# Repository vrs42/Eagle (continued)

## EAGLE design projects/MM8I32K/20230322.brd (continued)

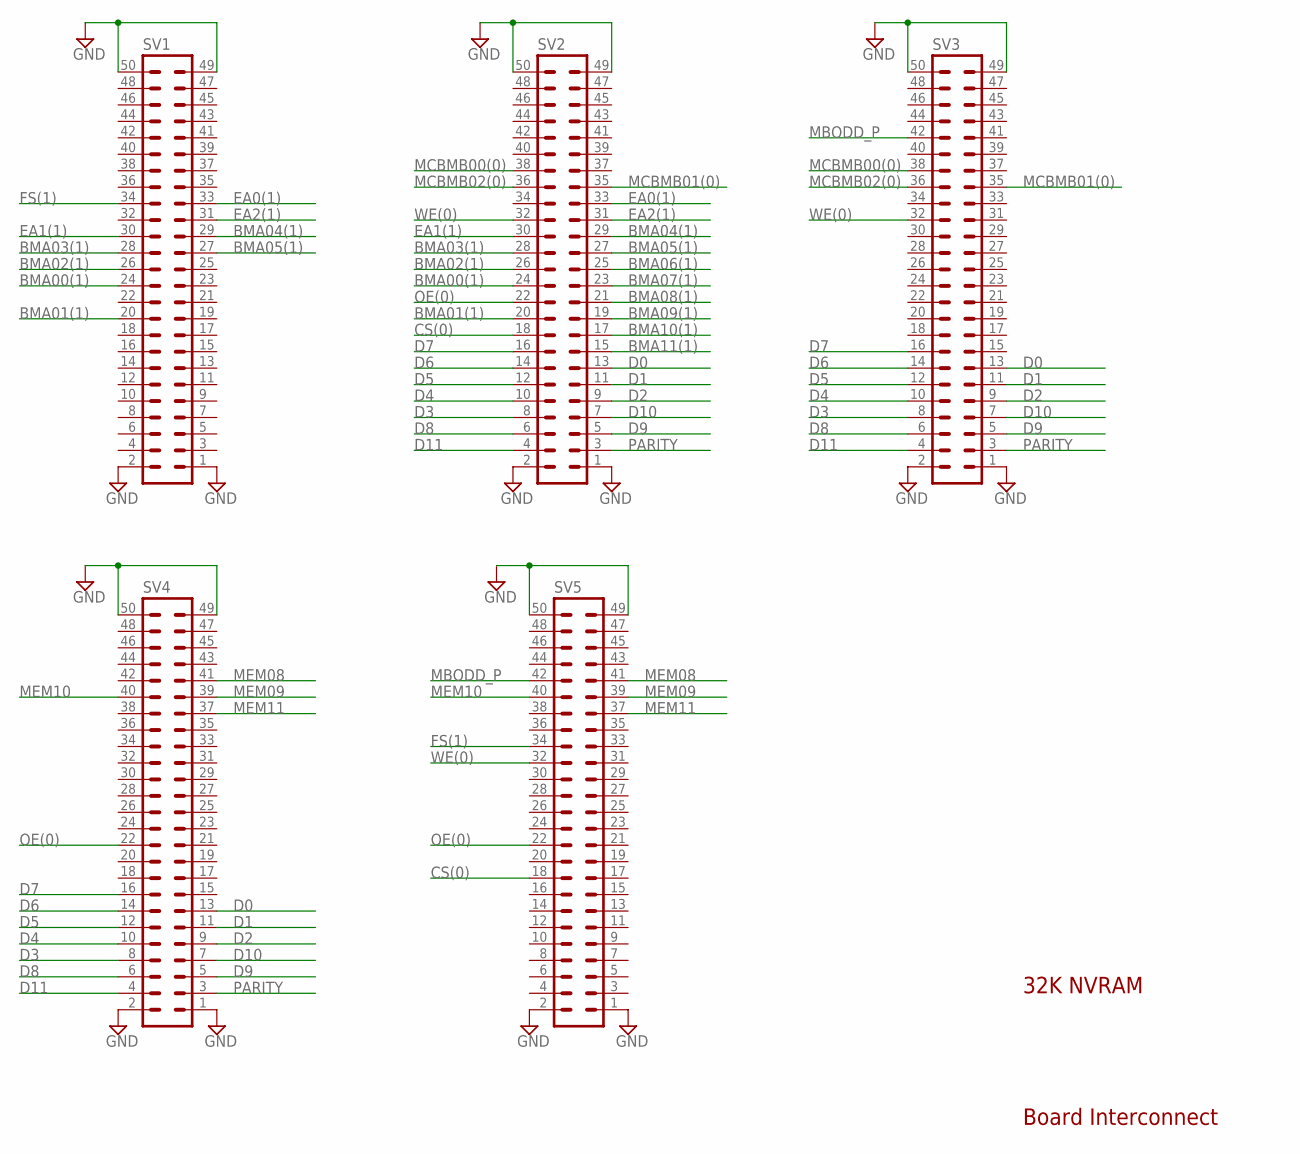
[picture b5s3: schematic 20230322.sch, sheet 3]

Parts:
SV1, SV2, SV3, SV4, SV5: ML50L

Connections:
BMA00(1): SV1.24, SV2.24; also elsewhere on the board
BMA01(1): SV1.20, SV2.20; also elsewhere on the board
BMA02(1): SV1.26, SV2.26; also elsewhere on the board
BMA03(1): SV1.28, SV2.28; also elsewhere on the board
BMA04(1): SV1.29, SV2.29; also elsewhere on the board
BMA05(1): SV1.27, SV2.27; also elsewhere on the board
BMA06(1): SV2.25; also elsewhere on the board
BMA07(1): SV2.23; also elsewhere on the board
BMA08(1): SV2.21; also elsewhere on the board
BMA09(1): SV2.19; also elsewhere on the board
BMA10(1): SV2.17; also elsewhere on the board
BMA11(1): SV2.15; also elsewhere on the board
CS(0): SV2.18, SV5.18; also elsewhere on the board
D0: SV2.13, SV3.13, SV4.13; also elsewhere on the board
D1: SV2.11, SV3.11, SV4.11; also elsewhere on the board
D2: SV2.9, SV3.9, SV4.9; also elsewhere on the board
D3: SV2.8, SV3.8, SV4.8; also elsewhere on the board
D4: SV2.10, SV3.10, SV4.10; also elsewhere on the board
D5: SV2.12, SV3.12, SV4.12; also elsewhere on the board
D6: SV2.14, SV3.14, SV4.14; also elsewhere on the board
D7: SV2.16, SV3.16, SV4.16; also elsewhere on the board
D8: SV2.6, SV3.6, SV4.6; also elsewhere on the board
D9: SV2.5, SV3.5, SV4.5; also elsewhere on the board
D10: SV2.7, SV3.7, SV4.7; also elsewhere on the board
D11: SV2.4, SV3.4, SV4.4; also elsewhere on the board
EA0(1): SV1.33, SV2.33; also elsewhere on the board
EA1(1): SV1.30, SV2.30; also elsewhere on the board
EA2(1): SV1.31, SV2.31; also elsewhere on the board
FS(1): SV1.34, SV5.34; also elsewhere on the board
GND: SV1.1, SV1.2, SV1.49, SV1.50, SV2.1, SV2.2, SV2.49, SV2.50, SV3.1, SV3.2, SV3.49, SV3.50, SV4.1, SV4.2, SV4.49, SV4.50, SV5.1, SV5.2, SV5.49, SV5.50; also elsewhere on the board
MBODD_P: SV3.42, SV5.42; also elsewhere on the board
MCBMB00(0): SV2.38, SV3.38; also elsewhere on the board
MCBMB01(0): SV2.35, SV3.35; also elsewhere on the board
MCBMB02(0): SV2.36, SV3.36; also elsewhere on the board
MEM08: SV4.41, SV5.41; also elsewhere on the board
MEM09: SV4.39, SV5.39; also elsewhere on the board
MEM10: SV4.40, SV5.40; also elsewhere on the board
MEM11: SV4.37, SV5.37; also elsewhere on the board
OE(0): SV2.22, SV4.22, SV5.22; also elsewhere on the board
PARITY: SV2.3, SV3.3, SV4.3; also elsewhere on the board
WE(0): SV2.32, SV3.32, SV5.32; also elsewhere on the board

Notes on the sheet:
32K NVRAM
Board Interconnect

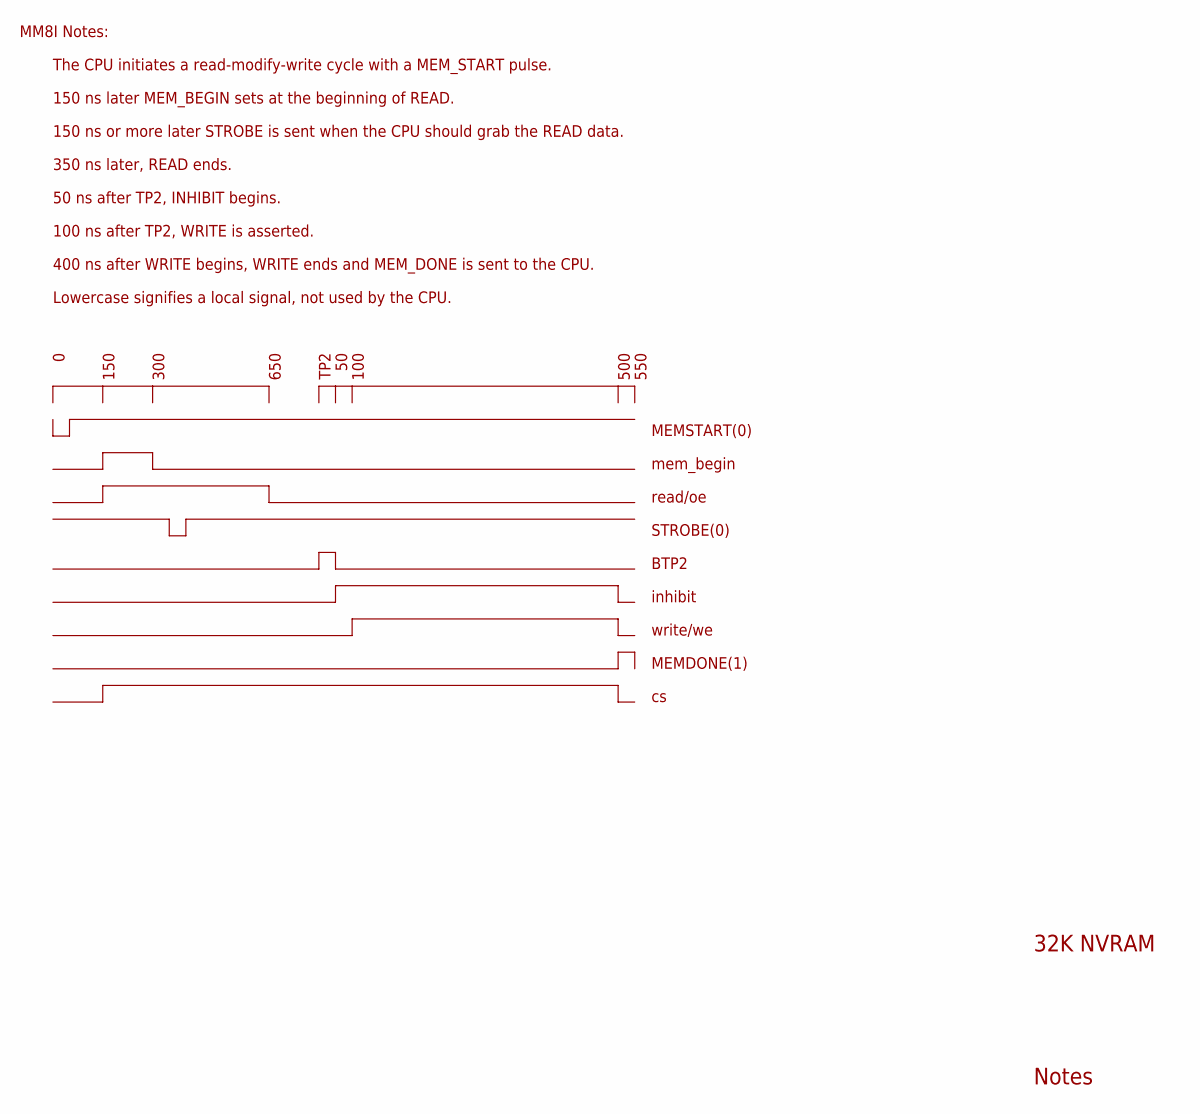
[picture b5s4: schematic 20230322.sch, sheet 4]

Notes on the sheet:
32K NVRAM
Notes
The CPU initiates a read-modify-write cycle with a MEM_START pulse.
150 ns later MEM_BEGIN sets at the beginning of READ.
150 ns or more later STROBE is sent when the CPU should grab the READ data.
50 ns after TP2, INHIBIT begins.
100 ns after TP2, WRITE is asserted.
400 ns after WRITE begins, WRITE ends and MEM_DONE is sent to the CPU.
350 ns later, READ ends.
150
300
650
TP2
100
500
MEMSTART(0)
mem_begin
read/oe
STROBE(0)
BTP2
inhibit
write/we
MEMDONE(1)
Lowercase signifies a local signal, not used by the CPU.
550
MM8I Notes:

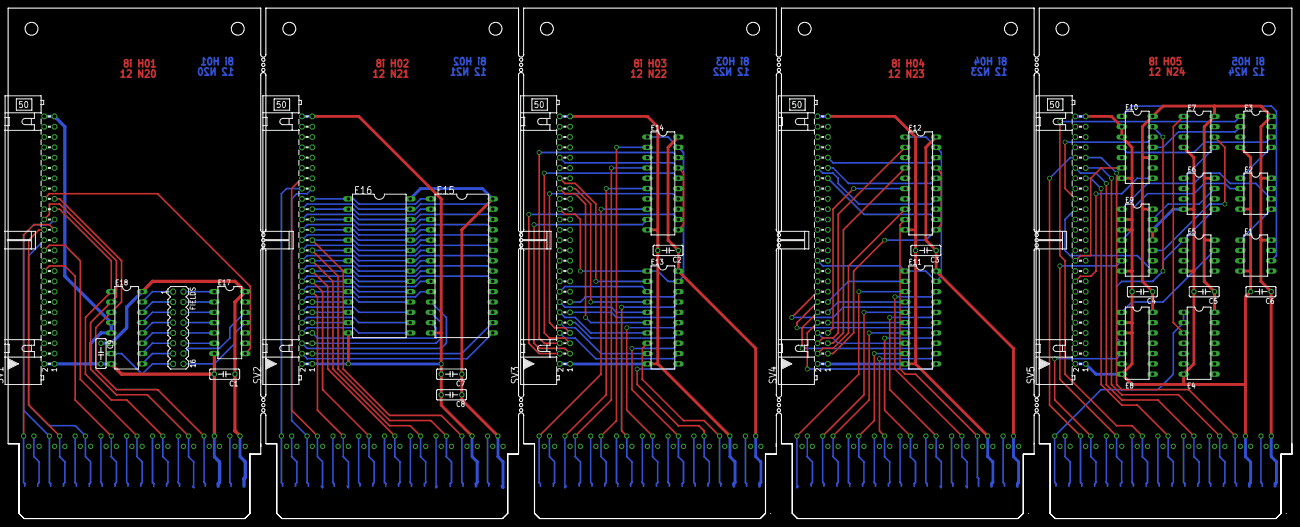
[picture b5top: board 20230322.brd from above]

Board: 2 copper layers, 316.2 x 125.7 mm, 44 parts (0 on the bottom side), 128 nets.

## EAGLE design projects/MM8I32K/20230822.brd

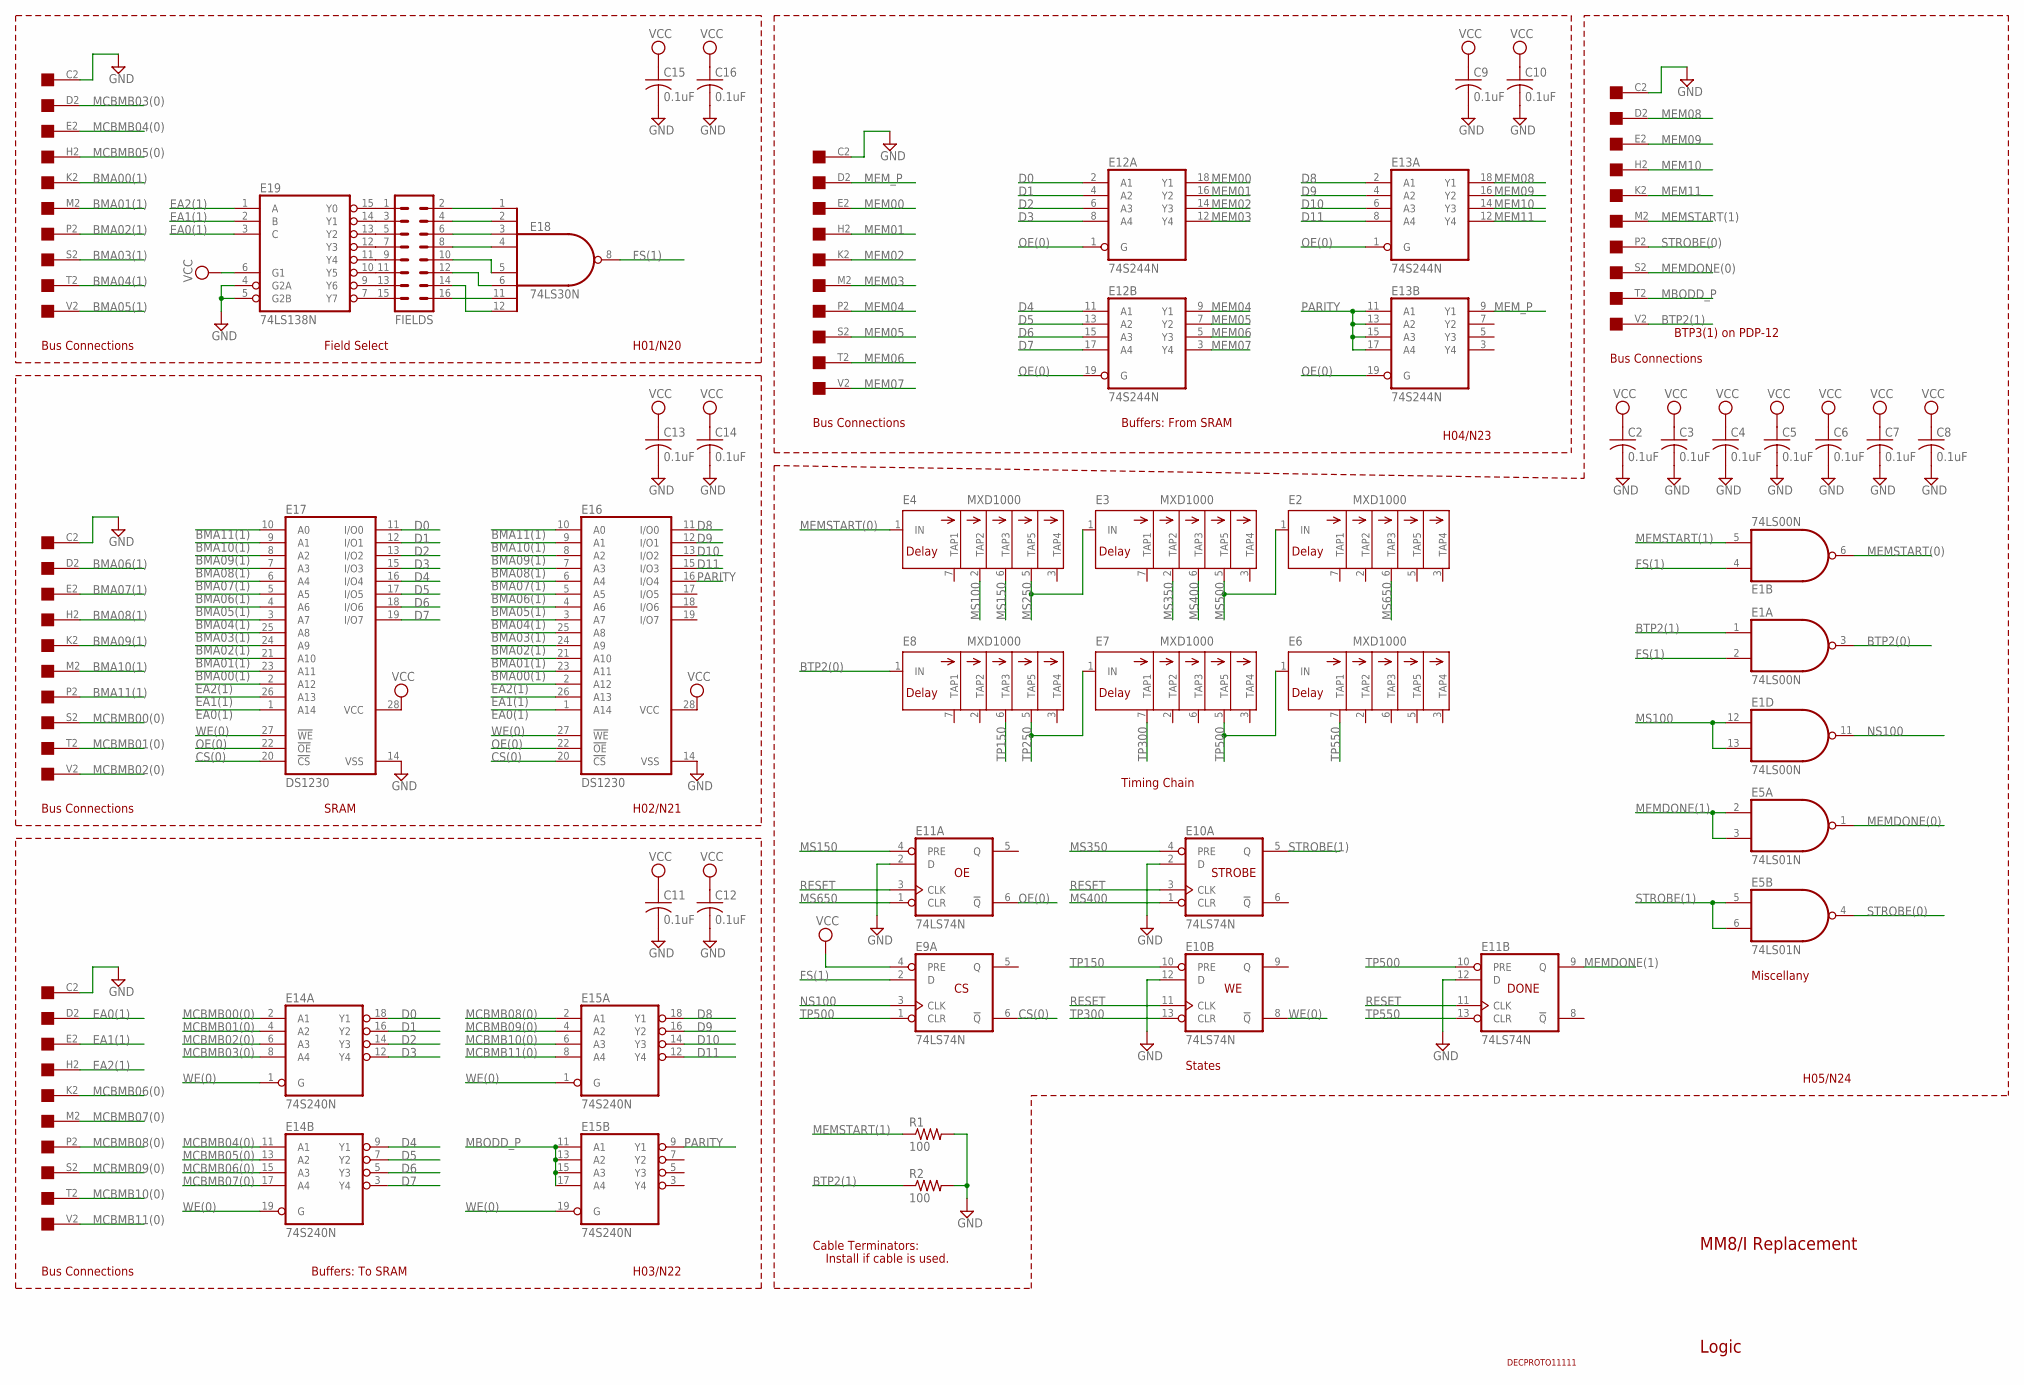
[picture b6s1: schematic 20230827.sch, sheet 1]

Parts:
C2, C3, C4, C5, C6, C7, C8, C9, C10, C11, C12, C13, C14, C15, C16: 0.1uF; C050-025X075
E1: 74LS00N; DIL14
E2, E3, E4, E6, E7, E8: MXD1000; DIL08
E5: 74LS01N; DIL14
E9, E10, E11: 74LS74N; DIL14
E12, E13: 74S244N; DIL20
E14, E15: 74S240N; DIL20
E16, E17: DS1230; DIL28-6
E18: 74LS30N; DIL14
E19: 74LS138N; DIL16
FIELDS: MA08-2
H01, H02, H03, H04, H05: EDGE-CON1
R1, R2: 100; 0207/10
U$6: DECPROTO11111

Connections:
BMA00(1): E16.23 (A11), E17.23 (A11), H01.K2; also elsewhere on the board
BMA01(1): E16.21 (A10), E17.21 (A10), H01.M2; also elsewhere on the board
BMA02(1): E16.24 (A9), E17.24 (A9), H01.P2; also elsewhere on the board
BMA03(1): E16.25 (A8), E17.25 (A8), H01.S2; also elsewhere on the board
BMA04(1): E16.3 (A7), E17.3 (A7), H01.T2; also elsewhere on the board
BMA05(1): E16.4 (A6), E17.4 (A6), H01.V2; also elsewhere on the board
BMA06(1): E16.5 (A5), E17.5 (A5), H02.D2; also elsewhere on the board
BMA07(1): E16.6 (A4), E17.6 (A4), H02.E2; also elsewhere on the board
BMA08(1): E16.7 (A3), E17.7 (A3), H02.H2; also elsewhere on the board
BMA09(1): E16.8 (A2), E17.8 (A2), H02.K2; also elsewhere on the board
BMA10(1): E16.9 (A1), E17.9 (A1), H02.M2; also elsewhere on the board
BMA11(1): E16.10 (A0), E17.10 (A0), H02.P2; also elsewhere on the board
BTP2(0): E1.3 (O), E8.1 (IN); also elsewhere on the board
BTP2(1): E1.1 (I0), H05.V2, R2.1
CS(0): E9.6 (!Q), E16.20 (!CS), E17.20 (!CS); also elsewhere on the board
D0: E12.2 (A1), E14.18 (Y1), E17.11 (I/O0); also elsewhere on the board
D1: E12.4 (A2), E14.16 (Y2), E17.12 (I/O1); also elsewhere on the board
D2: E12.6 (A3), E14.14 (Y3), E17.13 (I/O2); also elsewhere on the board
D3: E12.8 (A4), E14.12 (Y4), E17.15 (I/O3); also elsewhere on the board
D4: E12.11 (A1), E14.9 (Y1), E17.16 (I/O4); also elsewhere on the board
D5: E12.13 (A2), E14.7 (Y2), E17.17 (I/O5); also elsewhere on the board
D6: E12.15 (A3), E14.5 (Y3), E17.18 (I/O6); also elsewhere on the board
D7: E12.17 (A4), E14.3 (Y4), E17.19 (I/O7); also elsewhere on the board
D8: E13.2 (A1), E15.18 (Y1), E16.11 (I/O0); also elsewhere on the board
D9: E13.4 (A2), E15.16 (Y2), E16.12 (I/O1); also elsewhere on the board
D10: E13.6 (A3), E15.14 (Y3), E16.13 (I/O2); also elsewhere on the board
D11: E13.8 (A4), E15.12 (Y4), E16.15 (I/O3); also elsewhere on the board
EA0(1): E16.1 (A14), E17.1 (A14), E19.3 (C), H03.D2; also elsewhere on the board
EA1(1): E16.26 (A13), E17.26 (A13), E19.2 (B), H03.E2; also elsewhere on the board
EA2(1): E16.2 (A12), E17.2 (A12), E19.1 (A), H03.H2; also elsewhere on the board
MBODD_P: E15.11 (A1), E15.13 (A2), E15.15 (A3), E15.17 (A4), H05.T2; also elsewhere on the board
MCBMB00(0): E14.2 (A1), H02.S2; also elsewhere on the board
MCBMB01(0): E14.4 (A2), H02.T2; also elsewhere on the board
MCBMB02(0): E14.6 (A3), H02.V2; also elsewhere on the board
MCBMB03(0): E14.8 (A4), H01.D2; also elsewhere on the board
MCBMB04(0): E14.11 (A1), H01.E2; also elsewhere on the board
MCBMB05(0): E14.13 (A2), H01.H2; also elsewhere on the board
MCBMB06(0): E14.15 (A3), H03.K2
MCBMB07(0): E14.17 (A4), H03.M2
MCBMB08(0): E15.2 (A1), H03.P2
MCBMB09(0): E15.4 (A2), H03.S2
MCBMB10(0): E15.6 (A3), H03.T2
MCBMB11(0): E15.8 (A4), H03.V2
MEM00: E12.18 (Y1), H04.E2
MEM01: E12.16 (Y2), H04.H2
MEM02: E12.14 (Y3), H04.K2
MEM03: E12.12 (Y4), H04.M2
MEM04: E12.9 (Y1), H04.P2
MEM05: E12.7 (Y2), H04.S2
MEM06: E12.5 (Y3), H04.T2
MEM07: E12.3 (Y4), H04.V2
MEM08: E13.18 (Y1), H05.D2; also elsewhere on the board
MEM09: E13.16 (Y2), H05.E2; also elsewhere on the board
MEM10: E13.14 (Y3), H05.H2; also elsewhere on the board
MEM11: E13.12 (Y4), H05.K2; also elsewhere on the board
MEMDONE(0): E5.1 (O), H05.S2
MEMDONE(1): E5.2 (I0), E5.3 (I1), E11.9 (Q); also elsewhere on the board
MEMSTART(0): E1.6 (O), E4.1 (IN); also elsewhere on the board
MEMSTART(1): E1.5 (I1), H05.M2, R1.1
MEM_P: E13.9 (Y1), H04.D2
MS100: E1.12 (I0), E1.13 (I1), E4.2 (TAP2)
MS150: E4.6 (TAP3), E11.4 (PRE)
MS250: E3.1 (IN), E4.5 (TAP5)
MS350: E3.2 (TAP2), E10.4 (PRE)
MS400: E3.6 (TAP3), E10.1 (CLR)
MS500: E2.1 (IN), E3.5 (TAP5)
MS650: E2.6 (TAP3), E11.1 (CLR)
unnamed: E19.15 (Y0), FIELDS.1
unnamed: E19.14 (Y1), FIELDS.3
unnamed: E19.13 (Y2), FIELDS.5
unnamed: E19.12 (Y3), FIELDS.7
unnamed: E19.11 (Y4), FIELDS.9
unnamed: E19.10 (Y5), FIELDS.11
unnamed: E19.9 (Y6), FIELDS.13
unnamed: E19.7 (Y7), FIELDS.15
unnamed: E18.4 (I3), FIELDS.8
unnamed: E18.3 (I2), FIELDS.6
unnamed: E18.2 (I1), FIELDS.4
unnamed: E18.1 (I0), FIELDS.2
unnamed: E18.5 (I4), FIELDS.10
unnamed: E18.6 (I5), FIELDS.12
unnamed: E18.12 (I7), FIELDS.14
unnamed: E18.11 (I6), FIELDS.16
OE(0): E11.6 (!Q), E12.1 (G), E12.19 (G), E13.1 (G), E13.19 (G), E16.22 (!OE), E17.22 (!OE); also elsewhere on the board
PARITY: E13.11 (A1), E13.13 (A2), E13.15 (A3), E13.17 (A4), E15.9 (Y1), E16.16 (I/O4); also elsewhere on the board
STROBE(0): E5.4 (O), H05.P2
STROBE(1): E5.5 (I0), E5.6 (I1), E10.5 (Q); also elsewhere on the board
TP150: E8.6 (TAP3), E10.10 (PRE)
TP250: E7.1 (IN), E8.5 (TAP5)
TP300: E7.7 (TAP1), E10.13 (CLR)
WE(0): E10.8 (!Q), E14.1 (G), E14.19 (G), E15.1 (G), E15.19 (G), E16.27 (!WE), E17.27 (!WE); also elsewhere on the board

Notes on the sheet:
STROBE
DONE
H01/N20
H02/N21
H03/N22
H04/N23
Field Select
SRAM
MM8/I Replacement
Buffers: To SRAM
Buffers: From SRAM
Timing Chain
States
BTP3(1) on PDP-12
Miscellany
H05/N24
Logic
Bus Connections
Cable Terminators:
Install if cable is used.

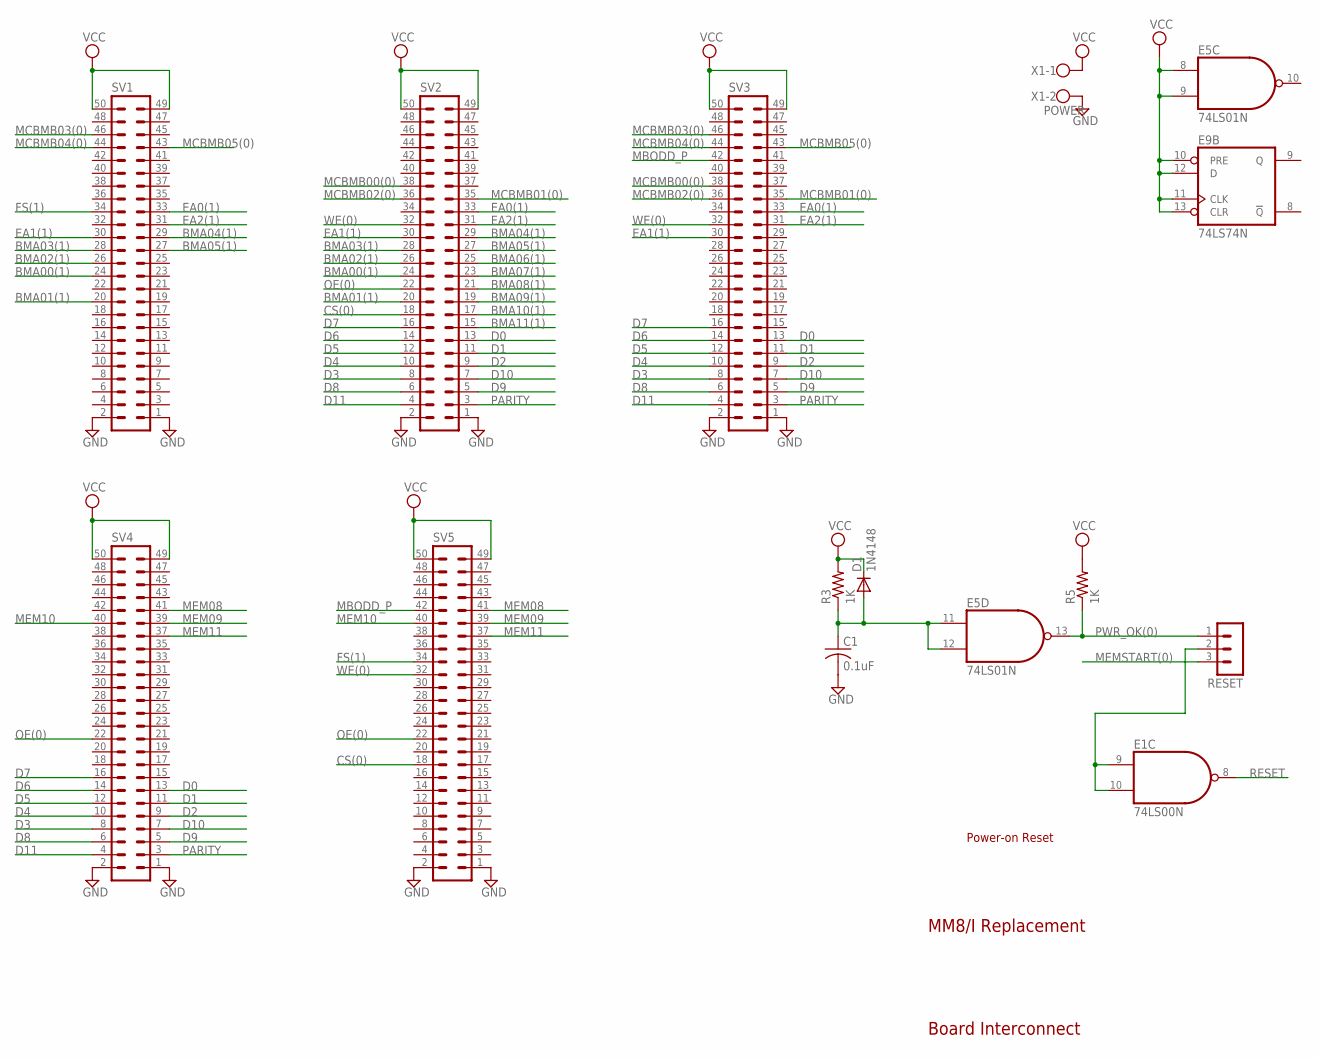
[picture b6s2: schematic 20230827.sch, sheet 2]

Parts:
C1: 0.1uF; C050-025X075
D1: 1N4148; DO35-10
E1: 74LS00N; DIL14
E5: 74LS01N; DIL14
E9: 74LS74N; DIL14
R3, R5: 1K; 0207/10
RESET: MA03-1
SV1, SV2, SV3, SV4, SV5: ML50L
X1: POWER; W237-102

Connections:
BMA00(1): SV1.24, SV2.24; also elsewhere on the board
BMA01(1): SV1.20, SV2.20; also elsewhere on the board
BMA02(1): SV1.26, SV2.26; also elsewhere on the board
BMA03(1): SV1.28, SV2.28; also elsewhere on the board
BMA04(1): SV1.29, SV2.29; also elsewhere on the board
BMA05(1): SV1.27, SV2.27; also elsewhere on the board
BMA06(1): SV2.25; also elsewhere on the board
BMA07(1): SV2.23; also elsewhere on the board
BMA08(1): SV2.21; also elsewhere on the board
BMA09(1): SV2.19; also elsewhere on the board
BMA10(1): SV2.17; also elsewhere on the board
BMA11(1): SV2.15; also elsewhere on the board
CS(0): SV2.18, SV5.18; also elsewhere on the board
D0: SV2.13, SV3.13, SV4.13; also elsewhere on the board
D1: SV2.11, SV3.11, SV4.11; also elsewhere on the board
D2: SV2.9, SV3.9, SV4.9; also elsewhere on the board
D3: SV2.8, SV3.8, SV4.8; also elsewhere on the board
D4: SV2.10, SV3.10, SV4.10; also elsewhere on the board
D5: SV2.12, SV3.12, SV4.12; also elsewhere on the board
D6: SV2.14, SV3.14, SV4.14; also elsewhere on the board
D7: SV2.16, SV3.16, SV4.16; also elsewhere on the board
D8: SV2.6, SV3.6, SV4.6; also elsewhere on the board
D9: SV2.5, SV3.5, SV4.5; also elsewhere on the board
D10: SV2.7, SV3.7, SV4.7; also elsewhere on the board
D11: SV2.4, SV3.4, SV4.4; also elsewhere on the board
EA0(1): SV1.33, SV2.33, SV3.33; also elsewhere on the board
EA1(1): SV1.30, SV2.30, SV3.30; also elsewhere on the board
EA2(1): SV1.31, SV2.31, SV3.31; also elsewhere on the board
MBODD_P: SV3.42, SV5.42; also elsewhere on the board
MCBMB00(0): SV2.38, SV3.38; also elsewhere on the board
MCBMB01(0): SV2.35, SV3.35; also elsewhere on the board
MCBMB02(0): SV2.36, SV3.36; also elsewhere on the board
MCBMB03(0): SV1.46, SV3.46; also elsewhere on the board
MCBMB04(0): SV1.44, SV3.44; also elsewhere on the board
MCBMB05(0): SV1.43, SV3.43; also elsewhere on the board
MEM08: SV4.41, SV5.41; also elsewhere on the board
MEM09: SV4.39, SV5.39; also elsewhere on the board
MEM10: SV4.40, SV5.40; also elsewhere on the board
MEM11: SV4.37, SV5.37; also elsewhere on the board
MEMSTART(0): RESET.3; also elsewhere on the board
unnamed: E1.9 (I0), E1.10 (I1), RESET.2
OE(0): SV2.22, SV4.22, SV5.22; also elsewhere on the board
PARITY: SV2.3, SV3.3, SV4.3; also elsewhere on the board
WE(0): SV2.32, SV3.32, SV5.32; also elsewhere on the board

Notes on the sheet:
Board Interconnect
MM8/I Replacement
Power-on Reset

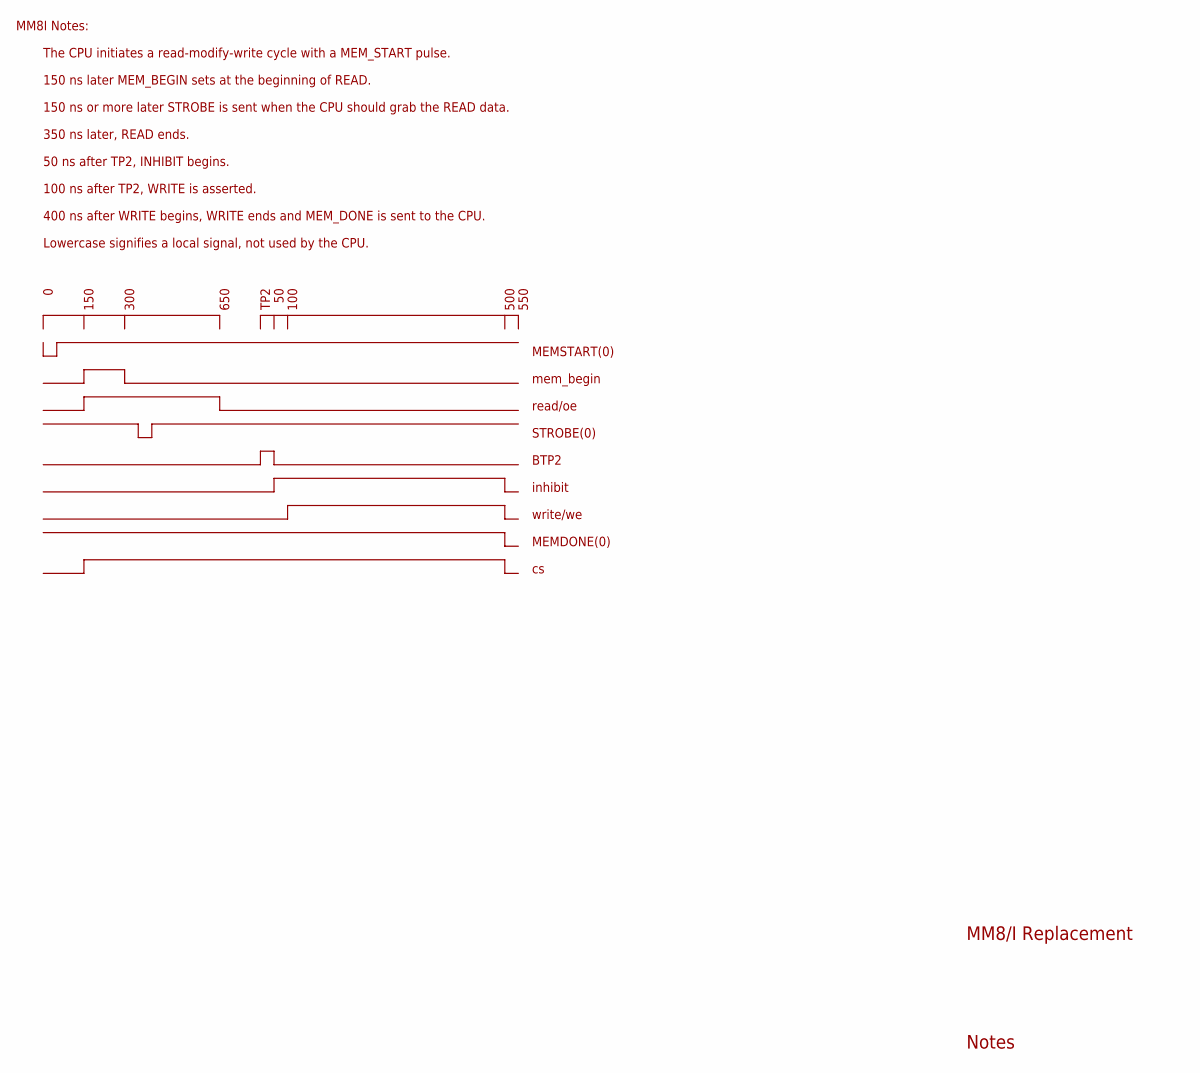
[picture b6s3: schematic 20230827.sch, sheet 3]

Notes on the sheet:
Notes
The CPU initiates a read-modify-write cycle with a MEM_START pulse.
150 ns later MEM_BEGIN sets at the beginning of READ.
150 ns or more later STROBE is sent when the CPU should grab the READ data.
50 ns after TP2, INHIBIT begins.
100 ns after TP2, WRITE is asserted.
400 ns after WRITE begins, WRITE ends and MEM_DONE is sent to the CPU.
350 ns later, READ ends.
150
300
650
TP2
100
500
MEMSTART(0)
mem_begin
read/oe
STROBE(0)
BTP2
inhibit
write/we
MEMDONE(0)
Lowercase signifies a local signal, not used by the CPU.
550
MM8I Notes:
MM8/I Replacement

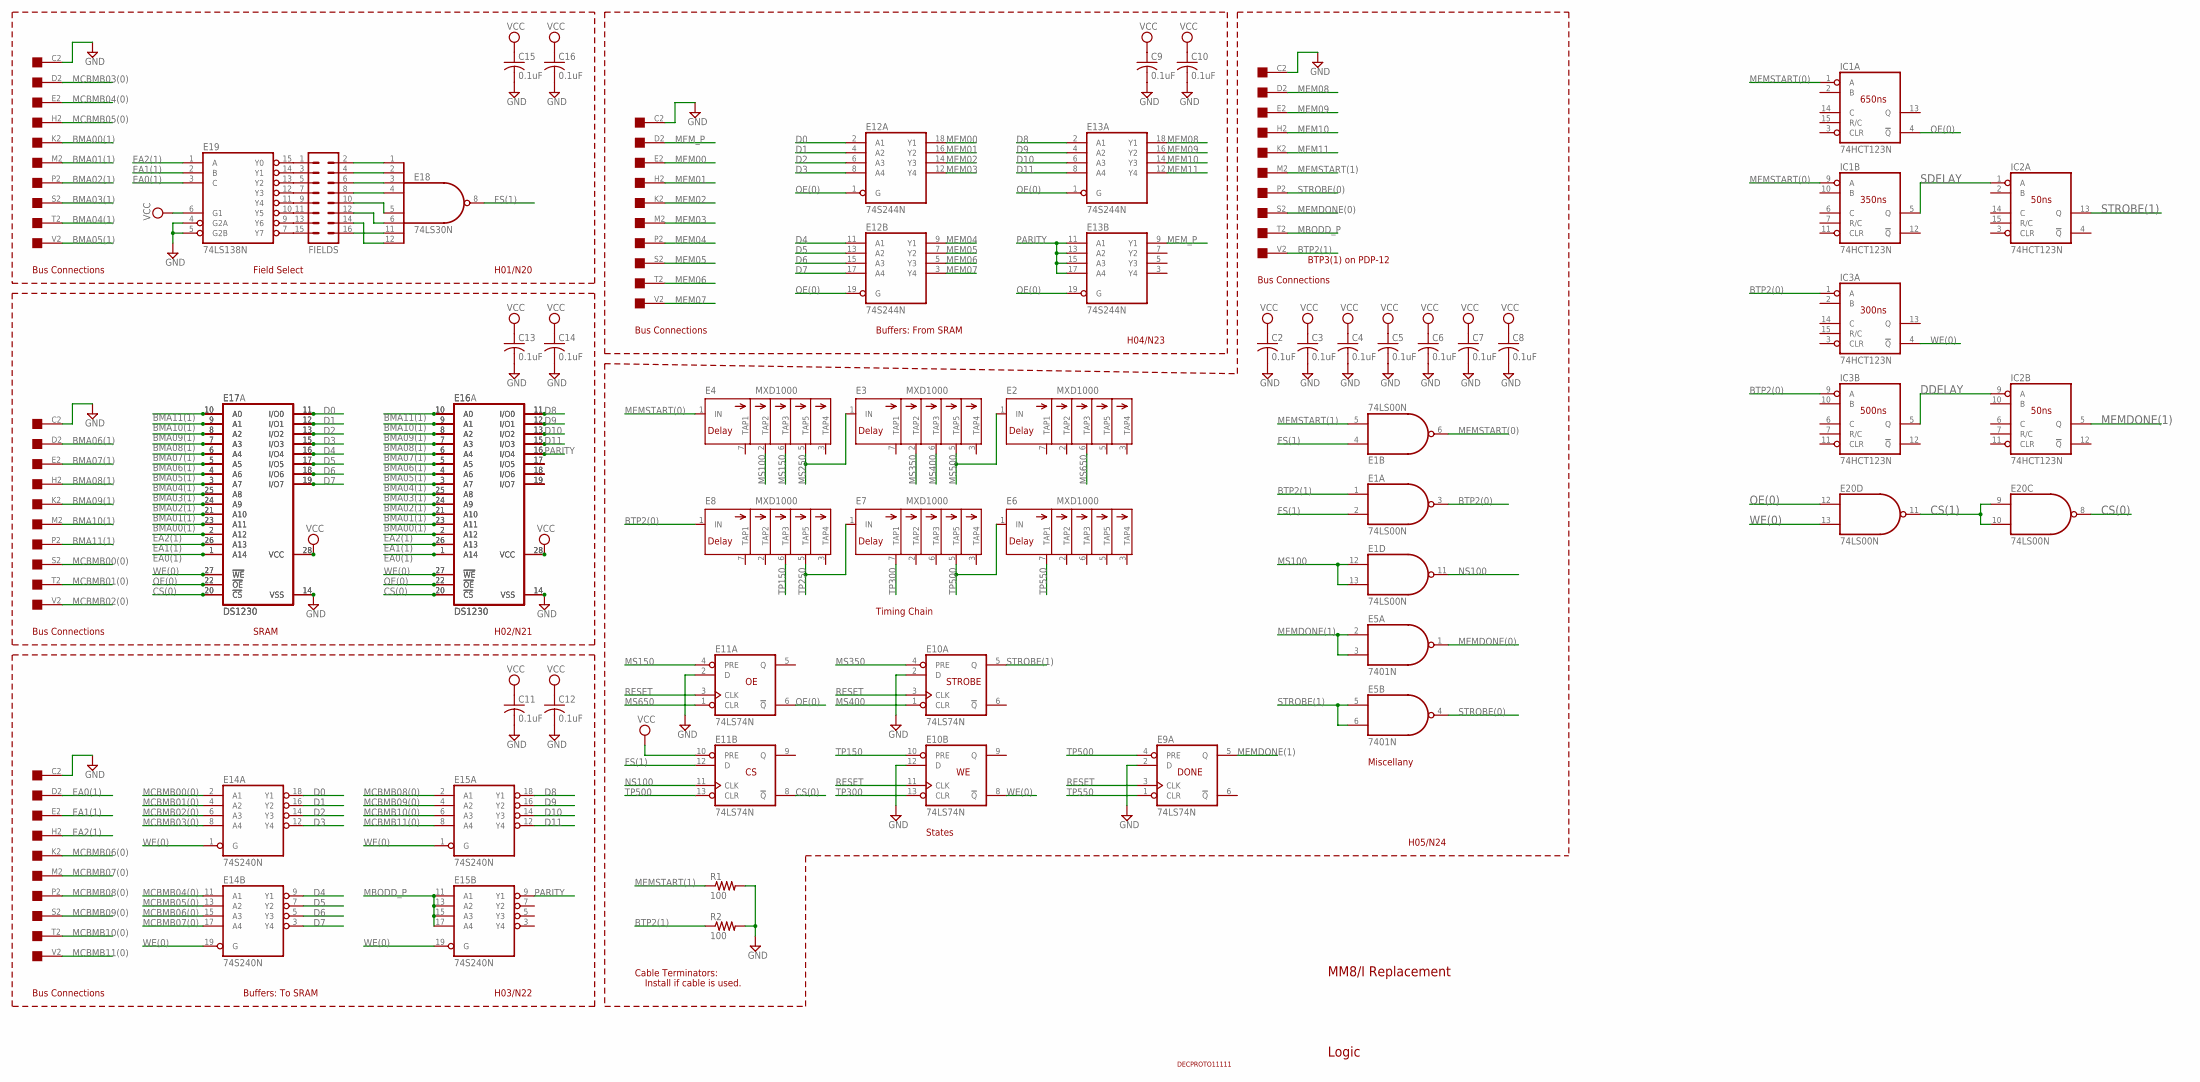
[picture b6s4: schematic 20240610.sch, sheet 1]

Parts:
C2, C3, C4, C5, C6, C7, C8, C9, C10, C11, C12, C13, C14, C15, C16: 0.1uF; C050-025X075
E1, E20: 74LS00N; DIL14
E2, E3, E4, E6, E7, E8: MXD1000; DIL08
E5: 7401N; DIL14
E9, E10, E11: 74LS74N; DIL14
E12, E13: 74S244N; DIL20
E14, E15: 74S240N; DIL20
E16, E17: DS1230; DIL28-6
E16A, E17A: DS1230; DIL28-3
E18: 74LS30N; DIL14
E19: 74LS138N; DIL16
FIELDS: MA08-2
H01, H02, H03, H04, H05: EDGE-CON1
IC1, IC2, IC3: 74HCT123N; DIL16
R1, R2: 100; 0207/10
U$6: DECPROTO11111

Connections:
BMA00(1): E16.23 (A11), E16A.23 (A11), E17.23 (A11), E17A.23 (A11), H01.K2; also elsewhere on the board
BMA01(1): E16.21 (A10), E16A.21 (A10), E17.21 (A10), E17A.21 (A10), H01.M2; also elsewhere on the board
BMA02(1): E16.24 (A9), E16A.24 (A9), E17.24 (A9), E17A.24 (A9), H01.P2; also elsewhere on the board
BMA03(1): E16.25 (A8), E16A.25 (A8), E17.25 (A8), E17A.25 (A8), H01.S2; also elsewhere on the board
BMA04(1): E16.3 (A7), E16A.3 (A7), E17.3 (A7), E17A.3 (A7), H01.T2; also elsewhere on the board
BMA05(1): E16.4 (A6), E16A.4 (A6), E17.4 (A6), E17A.4 (A6), H01.V2; also elsewhere on the board
BMA06(1): E16.5 (A5), E16A.5 (A5), E17.5 (A5), E17A.5 (A5), H02.D2; also elsewhere on the board
BMA07(1): E16.6 (A4), E16A.6 (A4), E17.6 (A4), E17A.6 (A4), H02.E2; also elsewhere on the board
BMA08(1): E16.7 (A3), E16A.7 (A3), E17.7 (A3), E17A.7 (A3), H02.H2; also elsewhere on the board
BMA09(1): E16.8 (A2), E16A.8 (A2), E17.8 (A2), E17A.8 (A2), H02.K2; also elsewhere on the board
BMA10(1): E16.9 (A1), E16A.9 (A1), E17.9 (A1), E17A.9 (A1), H02.M2; also elsewhere on the board
BMA11(1): E16.10 (A0), E16A.10 (A0), E17.10 (A0), E17A.10 (A0), H02.P2; also elsewhere on the board
BTP2(0): E1.3 (O), E8.1 (IN), IC3.1 (A), IC3.9 (A)
BTP2(1): E1.1 (I0), H05.V2, R2.1
CS(0): E11.8 (!Q), E16.20 (!CS), E16A.20 (!CS), E17.20 (!CS), E17A.20 (!CS), E20.8 (O); also elsewhere on the board
D0: E12.2 (A1), E14.18 (Y1), E17.11 (I/O0), E17A.11 (I/O0); also elsewhere on the board
D1: E12.4 (A2), E14.16 (Y2), E17.12 (I/O1), E17A.12 (I/O1); also elsewhere on the board
D2: E12.6 (A3), E14.14 (Y3), E17.13 (I/O2), E17A.13 (I/O2); also elsewhere on the board
D3: E12.8 (A4), E14.12 (Y4), E17.15 (I/O3), E17A.15 (I/O3); also elsewhere on the board
D4: E12.11 (A1), E14.9 (Y1), E17.16 (I/O4), E17A.16 (I/O4); also elsewhere on the board
D5: E12.13 (A2), E14.7 (Y2), E17.17 (I/O5), E17A.17 (I/O5); also elsewhere on the board
D6: E12.15 (A3), E14.5 (Y3), E17.18 (I/O6), E17A.18 (I/O6); also elsewhere on the board
D7: E12.17 (A4), E14.3 (Y4), E17.19 (I/O7), E17A.19 (I/O7); also elsewhere on the board
D8: E13.2 (A1), E15.18 (Y1), E16.11 (I/O0), E16A.11 (I/O0); also elsewhere on the board
D9: E13.4 (A2), E15.16 (Y2), E16.12 (I/O1), E16A.12 (I/O1); also elsewhere on the board
D10: E13.6 (A3), E15.14 (Y3), E16.13 (I/O2), E16A.13 (I/O2); also elsewhere on the board
D11: E13.8 (A4), E15.12 (Y4), E16.15 (I/O3), E16A.15 (I/O3); also elsewhere on the board
EA0(1): E16.1 (A14), E16A.1 (A14), E17.1 (A14), E17A.1 (A14), E19.3 (C), H03.D2; also elsewhere on the board
EA1(1): E16.26 (A13), E16A.26 (A13), E17.26 (A13), E17A.26 (A13), E19.2 (B), H03.E2; also elsewhere on the board
EA2(1): E16.2 (A12), E16A.2 (A12), E17.2 (A12), E17A.2 (A12), E19.1 (A), H03.H2; also elsewhere on the board
MBODD_P: E15.11 (A1), E15.13 (A2), E15.15 (A3), E15.17 (A4), H05.T2; also elsewhere on the board
MCBMB00(0): E14.2 (A1), H02.S2; also elsewhere on the board
MCBMB01(0): E14.4 (A2), H02.T2; also elsewhere on the board
MCBMB02(0): E14.6 (A3), H02.V2; also elsewhere on the board
MCBMB03(0): E14.8 (A4), H01.D2; also elsewhere on the board
MCBMB04(0): E14.11 (A1), H01.E2; also elsewhere on the board
MCBMB05(0): E14.13 (A2), H01.H2; also elsewhere on the board
MCBMB06(0): E14.15 (A3), H03.K2
MCBMB07(0): E14.17 (A4), H03.M2
MCBMB08(0): E15.2 (A1), H03.P2
MCBMB09(0): E15.4 (A2), H03.S2
MCBMB10(0): E15.6 (A3), H03.T2
MCBMB11(0): E15.8 (A4), H03.V2
MEM00: E12.18 (Y1), H04.E2
MEM01: E12.16 (Y2), H04.H2
MEM02: E12.14 (Y3), H04.K2
MEM03: E12.12 (Y4), H04.M2
MEM04: E12.9 (Y1), H04.P2
MEM05: E12.7 (Y2), H04.S2
MEM06: E12.5 (Y3), H04.T2
MEM07: E12.3 (Y4), H04.V2
MEM08: E13.18 (Y1), H05.D2; also elsewhere on the board
MEM09: E13.16 (Y2), H05.E2; also elsewhere on the board
MEM10: E13.14 (Y3), H05.H2; also elsewhere on the board
MEM11: E13.12 (Y4), H05.K2; also elsewhere on the board
MEMDONE(0): E5.1 (O), H05.S2
MEMDONE(1): E5.2 (I0), E5.3 (I1), E9.5 (Q), IC2.5 (Q); also elsewhere on the board
MEMSTART(0): E1.6 (O), E4.1 (IN), IC1.1 (A), IC1.9 (A); also elsewhere on the board
MEMSTART(1): E1.5 (I1), H05.M2, R1.1
MEM_P: E13.9 (Y1), H04.D2
MS100: E1.12 (I0), E1.13 (I1), E4.2 (TAP2)
MS150: E4.6 (TAP3), E11.4 (PRE)
MS250: E3.1 (IN), E4.5 (TAP5)
MS350: E3.2 (TAP2), E10.4 (PRE)
MS400: E3.6 (TAP3), E10.1 (CLR)
MS500: E2.1 (IN), E3.5 (TAP5)
MS650: E2.6 (TAP3), E11.1 (CLR)
unnamed: E19.15 (Y0), FIELDS.1
unnamed: E19.14 (Y1), FIELDS.3
unnamed: E19.13 (Y2), FIELDS.5
unnamed: E19.12 (Y3), FIELDS.7
unnamed: E19.11 (Y4), FIELDS.9
unnamed: E19.10 (Y5), FIELDS.11
unnamed: E19.9 (Y6), FIELDS.13
unnamed: E19.7 (Y7), FIELDS.15
unnamed: E18.4 (I3), FIELDS.8
unnamed: E18.3 (I2), FIELDS.6
unnamed: E18.2 (I1), FIELDS.4
unnamed: E18.1 (I0), FIELDS.2
unnamed: E18.5 (I4), FIELDS.10
unnamed: E18.6 (I5), FIELDS.12
unnamed: E18.12 (I7), FIELDS.14
unnamed: E18.11 (I6), FIELDS.16
unnamed: E16.17 (I/O5), E16A.17 (I/O5)
unnamed: E16.18 (I/O6), E16A.18 (I/O6)
unnamed: E16.19 (I/O7), E16A.19 (I/O7)
unnamed: E20.9 (I0), E20.10 (I1), E20.11 (O)
unnamed: IC1.5 (Q), IC2.1 (A)
unnamed: IC2.9 (A), IC3.5 (Q)
OE(0): E11.6 (!Q), E12.1 (G), E12.19 (G), E13.1 (G), E13.19 (G), E16.22 (!OE), E16A.22 (!OE), E17.22 (!OE), E17A.22 (!OE), E20.12 (I0), IC1.4 (!Q); also elsewhere on the board
PARITY: E13.11 (A1), E13.13 (A2), E13.15 (A3), E13.17 (A4), E15.9 (Y1), E16.16 (I/O4), E16A.16 (I/O4); also elsewhere on the board
STROBE(0): E5.4 (O), H05.P2
STROBE(1): E5.5 (I0), E5.6 (I1), E10.5 (Q), IC2.13 (Q)
TP150: E8.6 (TAP3), E10.10 (PRE)
TP250: E7.1 (IN), E8.5 (TAP5)
TP300: E7.7 (TAP1), E10.13 (CLR)
WE(0): E10.8 (!Q), E14.1 (G), E14.19 (G), E15.1 (G), E15.19 (G), E16.27 (!WE), E16A.27 (!WE), E17.27 (!WE), E17A.27 (!WE), E20.13 (I1), IC3.4 (!Q); also elsewhere on the board

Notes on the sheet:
STROBE
DONE
H01/N20
H02/N21
H03/N22
H04/N23
Field Select
SRAM
MM8/I Replacement
Buffers: To SRAM
Buffers: From SRAM
Timing Chain
States
BTP3(1) on PDP-12
Miscellany
H05/N24
Logic
Bus Connections
Cable Terminators:
Install if cable is used.
650ns
350ns
50ns
300ns
500ns
